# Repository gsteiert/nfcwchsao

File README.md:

# NFCWCHSAO B4
# Beeping Blinking Badge Buddy

This board has an engergy harvesting NFC EEPROM and WCH CH32V003 MCU.  
The MCU is connected to an RGB LED and piezo buzzer.
The two ICs are 8 pin SOIC, and the passives are 0603 so it is not too dificult to hand assemble, except for the RGB LED that is a little fine pitch, but the pads are extended and the close pins are shorted together anyway so it is not too difficult.

This board is designed for and looks great in OSH Park After Dark

[Order from OSH Park](https://oshpark.com/shared_projects/BUIwWMCI)
Be sure to choose the "After Dark" option to get the same results as in the picture.

## Components
 * [NT3H2211W0FT1X](https://www.mouser.com/ProductDetail/771-NT3H2211W0FT1X) 
 * [CH32V003J4M6](https://www.lcsc.com/product-detail/Microcontroller-Units-MCUs-MPUs-SOCs_WCH-Jiangsu-Qin-Heng-CH32V003J4M6_C5346354.html) 
 * [PKLCS1212E20A0-R1](https://www.mouser.com/ProductDetail/81-PKLCS1212E20A0-R1) 
 * [QLS6A-FKW-CNSNSF043](https://www.mouser.com/ProductDetail/941-QLS6AFKWNSNSF043) 
 * 1.0uF 0603 Capacitor
 * 4x 10K 0603 Resistors

## Schematic
[View Schematic online in KiCanvas](https://kicanvas.org/?github=https%3A%2F%2Fgithub.com%2Fgsteiert%2Fnfcwchsao%2Fblob%2Fmain%2Fbrd%2Fnfcwchsao.kicad_sch)

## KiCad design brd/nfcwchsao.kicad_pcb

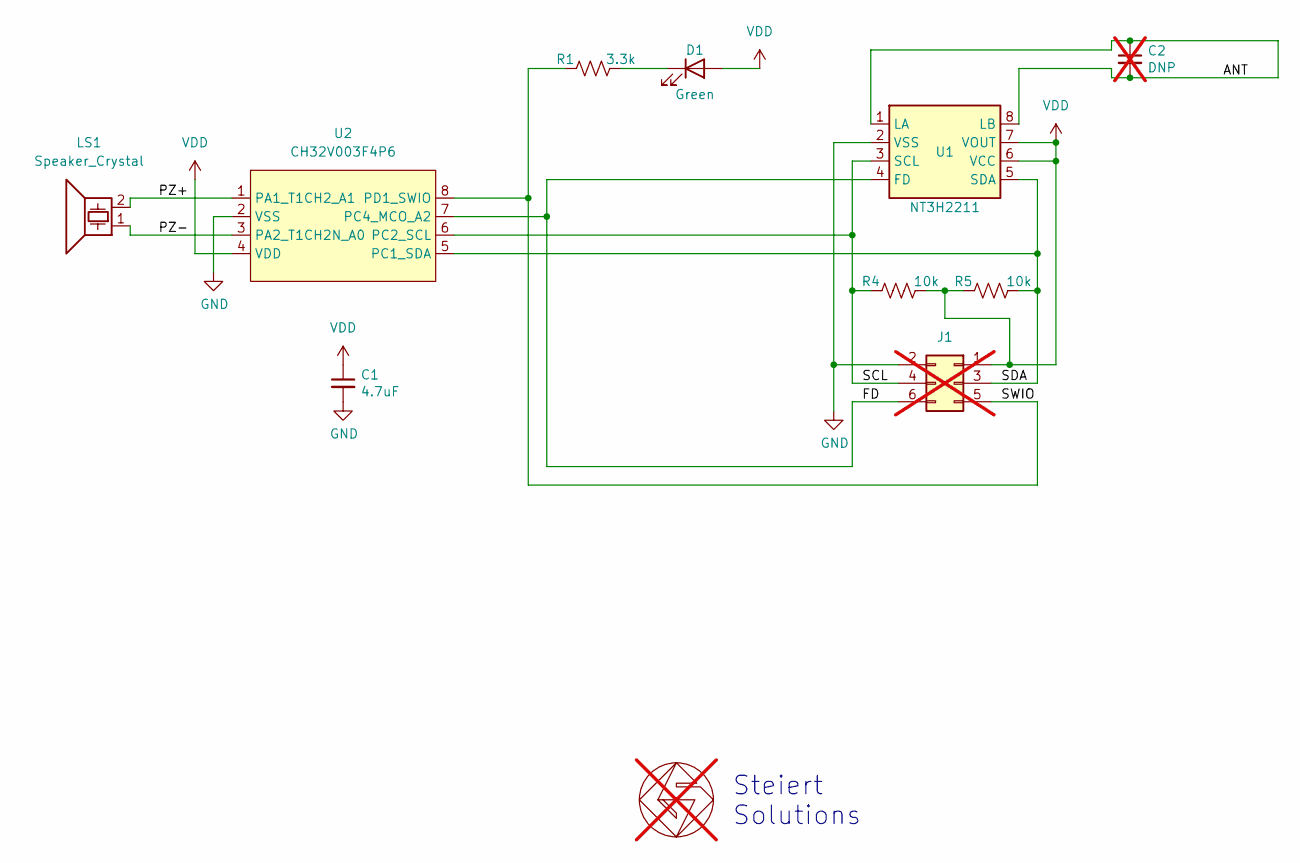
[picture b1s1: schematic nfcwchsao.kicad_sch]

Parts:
C1: 4.7uF; C_0603_1608Metric_Pad1.08x0.95mm_HandSolder; MPN CL10A475KP8NNNC; LCSC C1705
C2: DNP; C_0603_1608Metric; not fitted
D1: Green; LED_Right_Angle_3x2x1mm; MPN HSMG-C110; LCSC C7202185
GS1: GS_logo; gs_logo_200mil; not fitted
J1: Conn_02x03_Odd_Even; PinHeader_2x03_P2.54mm_Staggered; not fitted
LS1: Speaker_Crystal; Buzzer_Murata_PKLCS1212E_handy; MPN PKLCS1212E20A0-R1; LCSC C3811858
R1: 3.3k; R_0603_1608Metric_Pad0.98x0.95mm_HandSolder; MPN RC0603FR-073K3L; LCSC C108078
R4, R5: 10k; R_0603_1608Metric_Pad0.98x0.95mm_HandSolder; MPN RC0603FR-0710KL; LCSC C98220
U1: NT3H2211; SO-8_3.9x4.9mm_P1.27mm; MPN NT3H2211W0FT1X; LCSC C2905792
U2: CH32V003F4P6; SOP-8_3.9x4.9mm_P1.27mm; MPN CH32V003J4M6; LCSC C5346354

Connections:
/ANT: C2.1, C2.2, U1.1 (LA), U1.8 (LB)
/FD: J1.6, U1.4 (FD), U2.7 (PC4_MCO_A2)
/PZ+: LS1.2, U2.1 (PA1_T1CH2_A1)
/PZ-: LS1.1, U2.3 (PA2_T1CH2N_A0)
/SCL: J1.4, R4.2, U1.3 (SCL), U2.6 (PC2_SCL)
/SDA: J1.3, R5.1, U1.5 (SDA), U2.5 (PC1_SDA)
/SWIO: J1.5, R1.2, U2.8 (PD1_SWIO)
GND: C1.2, J1.2, U1.2 (VSS), U2.2 (VSS)
unnamed: D1.1 (K), R1.1
VDD: C1.1, D1.2 (A), J1.1, R4.1, R5.2, U1.6 (VCC), U1.7 (VOUT), U2.4 (VDD)

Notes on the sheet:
Steiert Solutions

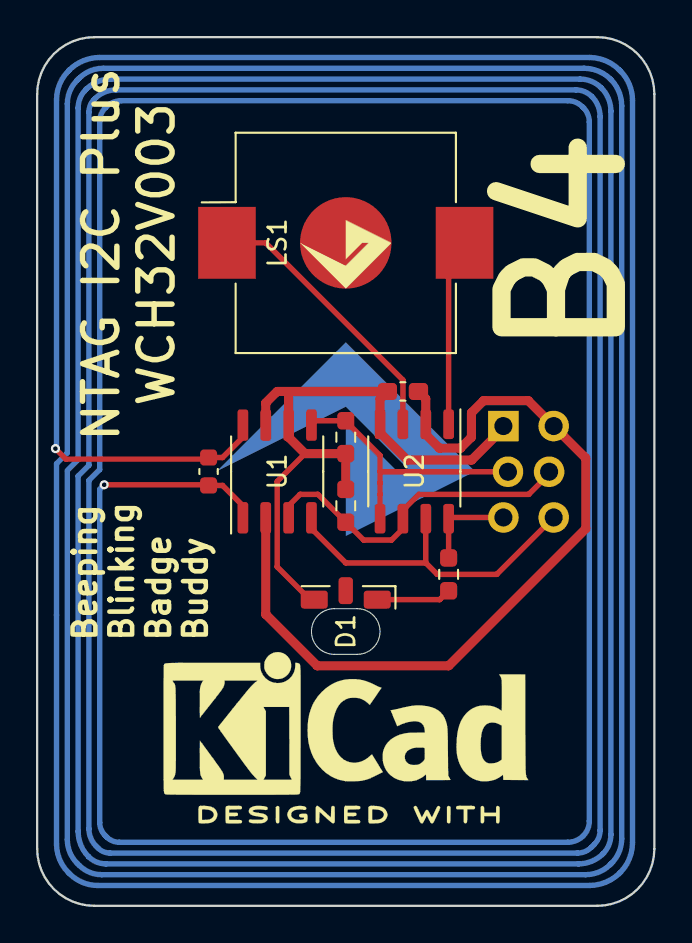
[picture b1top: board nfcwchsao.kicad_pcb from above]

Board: 2 copper layers, 34.3 x 48.3 mm, 11 parts (0 on the bottom side), 10 nets.

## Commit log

2024-05-12 checking in complete design
2024-05-12 updating part numbers and documenation
2024-05-13 updated README with more details and pictures
2024-05-14 add note for after dark option
2024-10-13 updating to hand solder buzzer footprint, staggered header, single color LED
2024-10-14 refining updates
2024-10-17 changing to CCO license
2024-10-27 cleaned up BOM, changed KiCad logo to all silkscreen
